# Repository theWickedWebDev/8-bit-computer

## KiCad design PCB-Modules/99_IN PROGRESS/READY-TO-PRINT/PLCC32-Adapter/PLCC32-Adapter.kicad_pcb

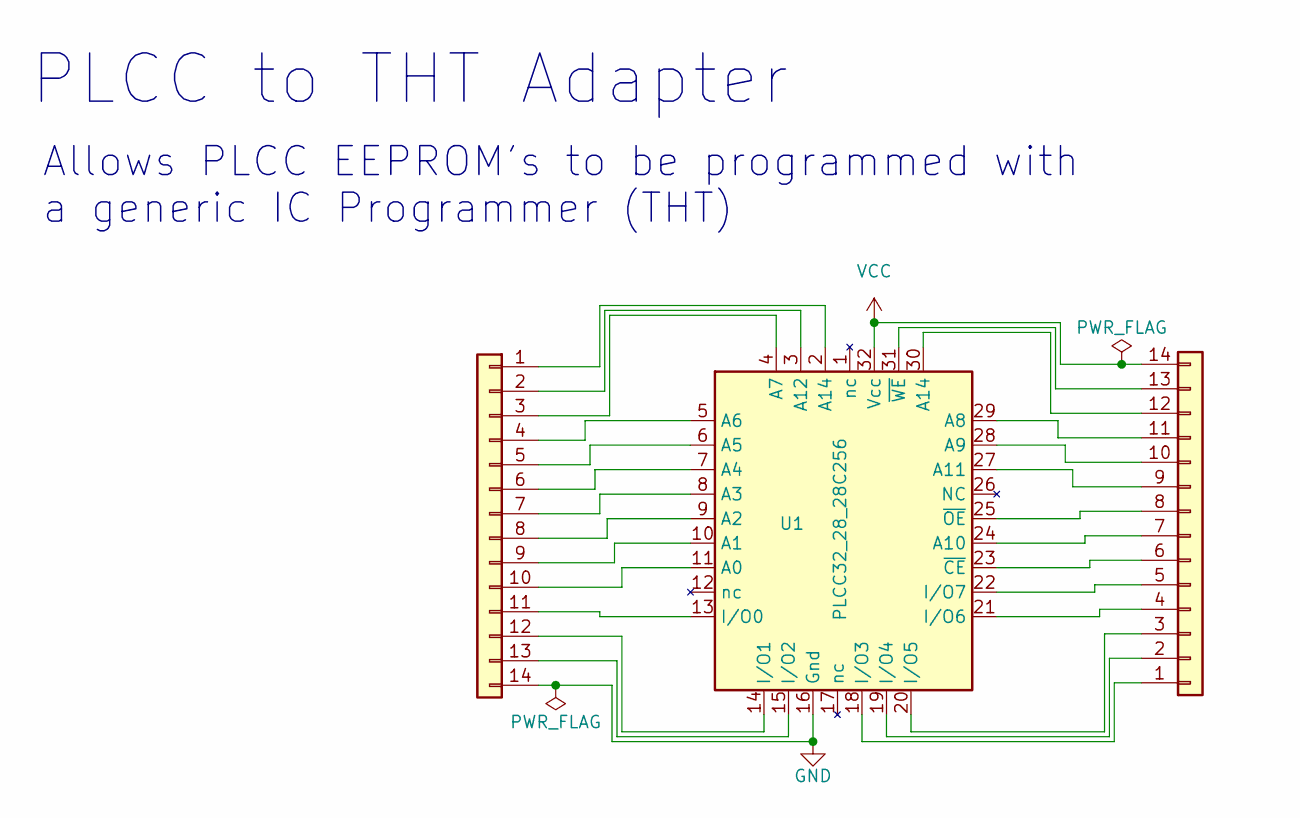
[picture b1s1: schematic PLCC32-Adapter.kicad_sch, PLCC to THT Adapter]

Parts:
J1, J2: Conn_01x14; PinHeader_1x14_P2.54mm_Vertical
U1: PLCC32_28_28C256; Microchip-32J-10_2001-B-IPC_A

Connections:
GND: J2.14, U1.16 (Gnd)
unnamed: J1.1, U1.18 (I/O3)
unnamed: J1.2, U1.19 (I/O4)
unnamed: J1.3, U1.20 (I/O5)
unnamed: J1.4, U1.21 (I/O6)
unnamed: J1.5, U1.22 (I/O7)
unnamed: J1.6, U1.23 (~CE)
unnamed: J1.7, U1.24 (A10)
unnamed: J1.8, U1.25 (~OE)
unnamed: J1.9, U1.27 (A11)
unnamed: J1.10, U1.28 (A9)
unnamed: J1.11, U1.29 (A8)
unnamed: J1.12, U1.30 (A14)
unnamed: J1.13, U1.31 (~WE)
unnamed: J2.1, U1.2 (A14)
unnamed: J2.2, U1.3 (A12)
unnamed: J2.3, U1.4 (A7)
unnamed: J2.4, U1.5 (A6)
unnamed: J2.5, U1.6 (A5)
unnamed: J2.6, U1.7 (A4)
unnamed: J2.7, U1.8 (A3)
unnamed: J2.8, U1.9 (A2)
unnamed: J2.9, U1.10 (A1)
unnamed: J2.10, U1.11 (A0)
unnamed: J2.11, U1.13 (I/O0)
unnamed: J2.12, U1.14 (I/O1)
unnamed: J2.13, U1.15 (I/O2)
VCC: J1.14, U1.32 (Vcc)

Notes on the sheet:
PLCC to THT Adapter
Allows PLCC EEPROM's to be programmed with a generic IC Programmer (THT)

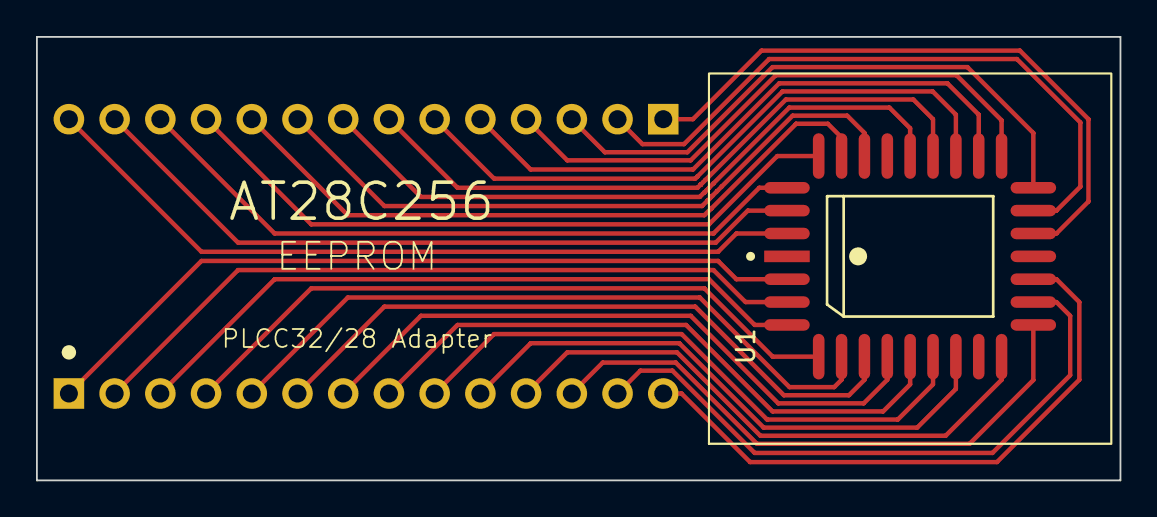
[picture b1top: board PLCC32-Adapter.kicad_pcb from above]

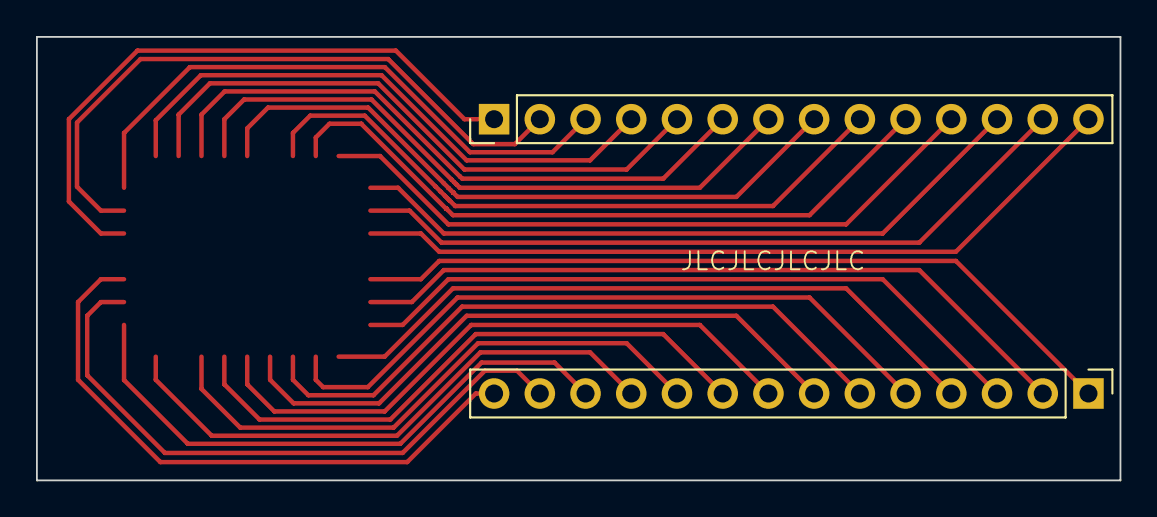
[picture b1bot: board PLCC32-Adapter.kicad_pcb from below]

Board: 2 copper layers, 60.2 x 24.6 mm, 3 parts (2 on the bottom side), 28 nets.

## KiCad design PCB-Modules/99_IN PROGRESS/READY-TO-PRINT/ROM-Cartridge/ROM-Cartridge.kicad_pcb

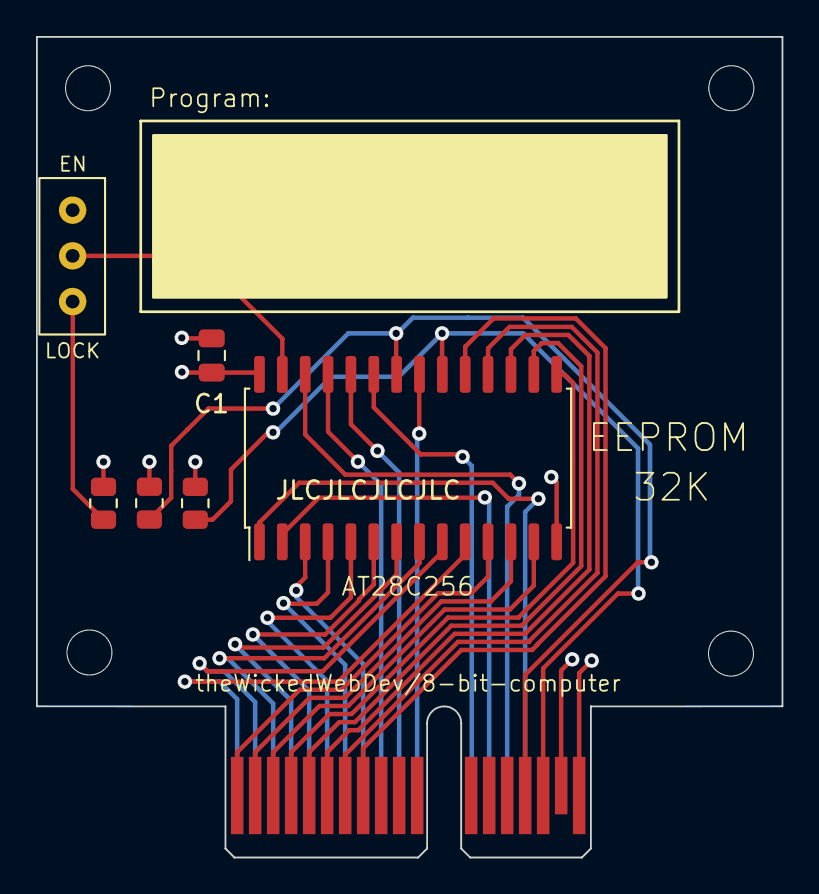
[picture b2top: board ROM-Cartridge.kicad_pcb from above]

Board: 4 copper layers, 41.4 x 45.6 mm, 7 parts (0 on the bottom side), 29 nets.

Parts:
C1: C; C_0805_2012Metric
J1: PCIE-Edge-Connect-036-02-X-D-RA_1; BUS_PCIexpress_x1
R1, R2, R3: R_Small_US; R_0805_2012Metric
SW1: SW_DPDT_x2; spdt-slide-switch
U1: 28C256; SOIC-28W_7.5x17.9mm_P1.27mm

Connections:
/A0: J1.A1 (A01), U1.10 (A0)
/A1: J1.A2 (A02), U1.9 (A1)
/A2: J1.A3 (A03), U1.8 (A2)
/A3: J1.A4 (A04), U1.7 (A3)
/A4: J1.A5 (A05), U1.6 (A4)
/A5: J1.A6 (A06), U1.5 (A5)
/A6: J1.A7 (A07), U1.4 (A6)
/A7: J1.A8 (A08), U1.3 (A7)
/A8: J1.A9 (A09), U1.25 (A8)
/A9: J1.A10, U1.24 (A9)
/A10: J1.A11, U1.21 (A10)
/A11: J1.A12, U1.23 (A11)
/A12: J1.A13, U1.2 (A12)
/A13: J1.A14, U1.26 (A13)
/A14: J1.A15, U1.1 (A14)
/D0: J1.B1 (B01), U1.11 (D0)
/D1: J1.B2 (B02), U1.12 (D1)
/D2: J1.B3 (B03), U1.13 (D2)
/D3: J1.B4 (B04), U1.15 (D3)
/D4: J1.B5 (B05), U1.16 (D4)
/D5: J1.B6 (B06), U1.17 (D5)
/D6: J1.B7 (B07), U1.18 (D6)
/D7: J1.B8 (B08), U1.19 (D7)
/~EN: J1.B16, R1.1, U1.20 (~CS)
/~READ: J1.B15, R2.1, U1.22 (~OE)
/~WRITE: R3.1, SW1.1 (A)
GND: C1.2, J1.B17, U1.14 (GND)
unnamed: SW1.2 (B), U1.27 (~WE)
VCC: C1.1, J1.B18, R1.2, R2.2, R3.2, U1.28 (VCC)

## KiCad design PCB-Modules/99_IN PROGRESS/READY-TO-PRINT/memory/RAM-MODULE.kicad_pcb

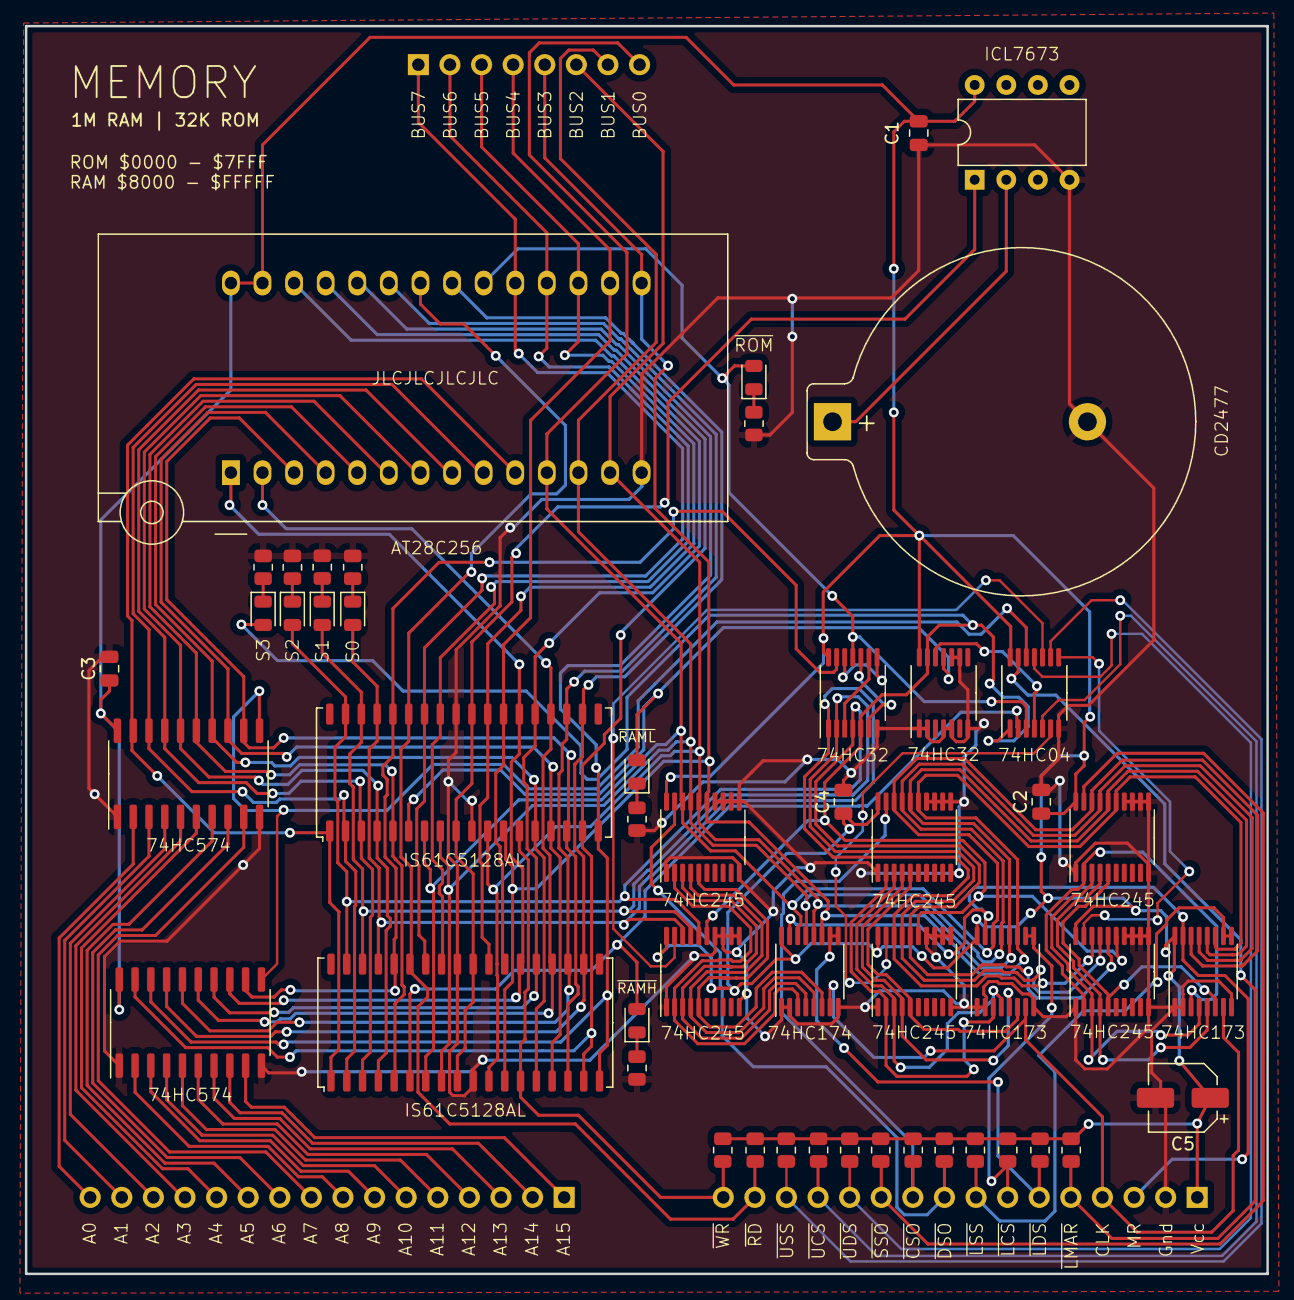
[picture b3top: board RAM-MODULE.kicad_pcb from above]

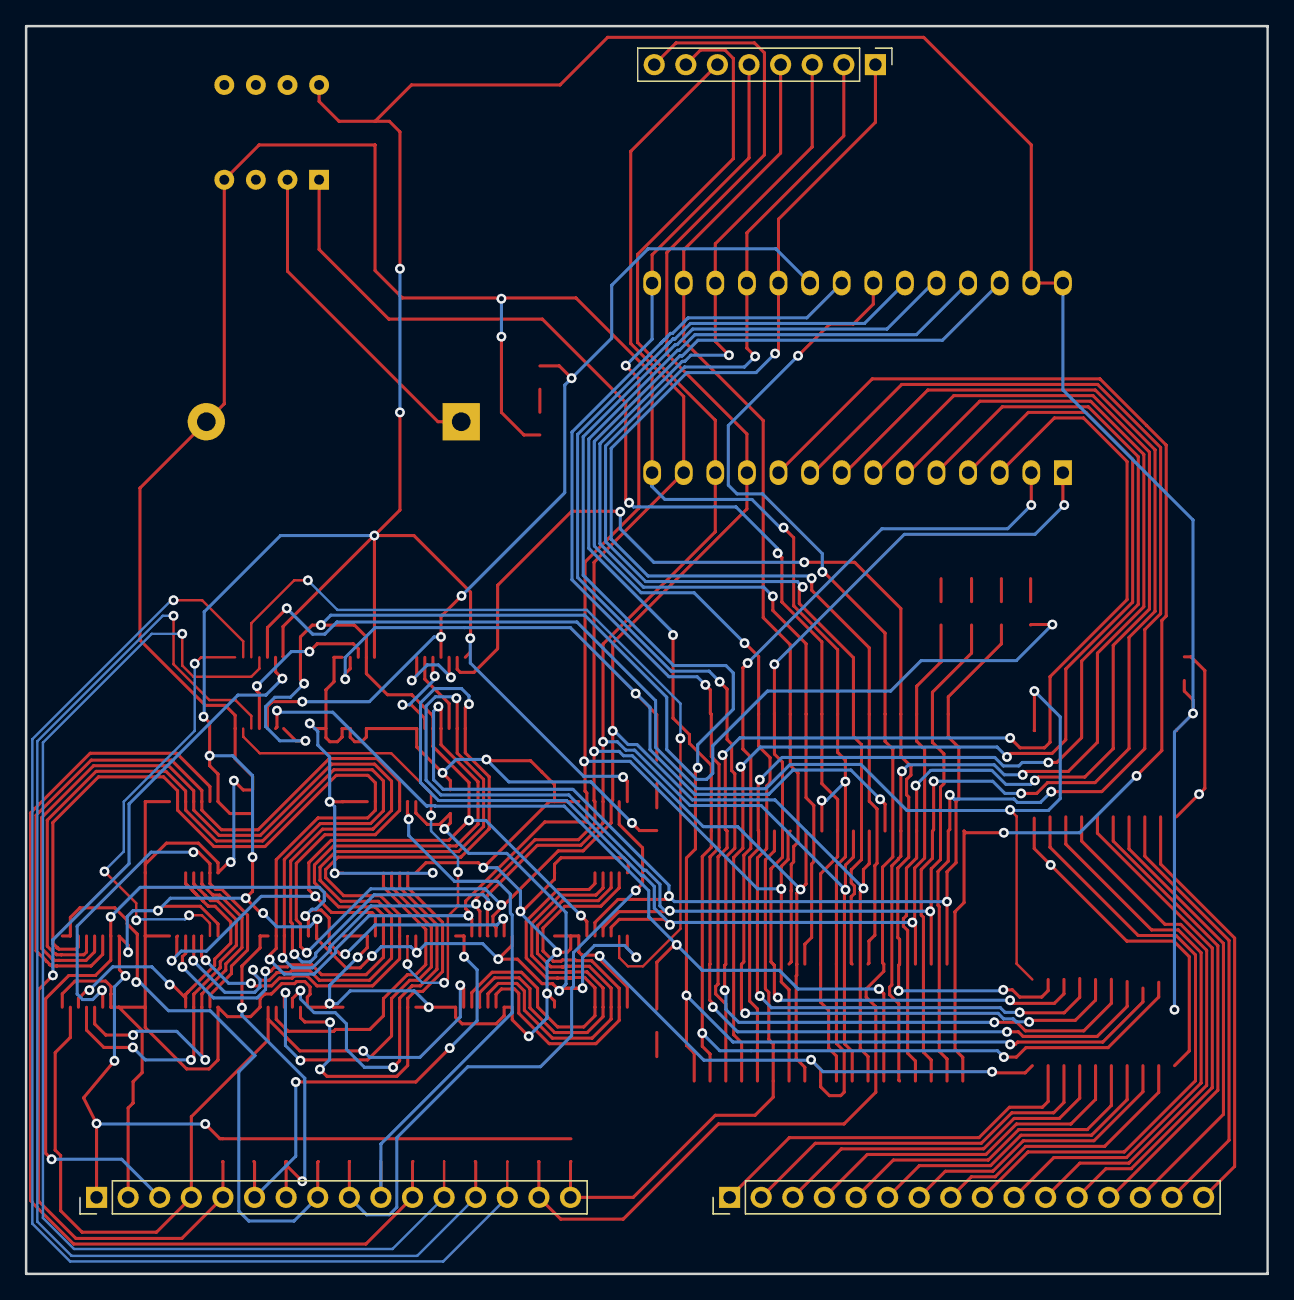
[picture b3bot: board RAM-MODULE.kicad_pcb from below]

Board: 4 copper layers, 99.8 x 100.3 mm, 53 parts (3 on the bottom side), 92 nets.

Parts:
BT1: Battery_Cell; BatteryHolder_Keystone_106_1x20mm
C1, C2, C3, C4: C; C_0805_2012Metric
C5: C_Polarized; CP_Elec_5x5.9
D3, D4, D5, D6, D7, D8, D9: LED; LED_0805_2012Metric
J1, J3: Conn_01x16; PinHeader_1x16_P2.54mm_Vertical
J2: Conn_01x08; PinHeader_1x08_P2.54mm_Vertical
R2, R3, R4, R5, R6, R7, R8, R9, R10, R11, R12, R13, R14, R15, R16, R17, R18, R19, R20: R_US; R_0805_2012Metric
U1: 28C256; DIP_Socket-28_W11.9_W12.7_W15.24_W17.78_W18.5_3M_228-1277-0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
U2, U4: 74LS574; SO-20_5.3x12.6mm_P1.27mm
U3, U5: IS61C5128AL-10KLI; SOJ-36_10.16x23.49mm_P1.27mm
U6, U9, U12: 74LS173; TSSOP-16_4.4x5mm_P0.65mm
U7, U8, U10, U11, U13, U14: 74LS245; TSSOP-20_4.4x6.5mm_P0.65mm
U15, U17: 74LS32; TSSOP-14_4.4x5mm_P0.65mm
U16: 74LS04; TSSOP-14_4.4x5mm_P0.65mm
U18: ICL7673; DIP-8_W7.62mm

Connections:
+5V: C1.1, C2.1, C3.1, C4.1, C5.1, J3.1, R2.1, R3.1, R4.1, R5.1, R6.1, R7.1, R8.1, R9.1, R10.1, R11.1, R12.1, R13.1, U1.27 (~WE), U1.28 (VCC), U2.20 (VCC), U4.20 (VCC), U6.16 (VCC), U7.20 (VCC), U8.20 (VCC), U9.16 (VCC), U10.20 (VCC), U11.20 (VCC), U12.16 (VCC), U13.20 (VCC), U14.20 (VCC), U15.14 (VCC), U16.14 (VCC), U17.14 (VCC), U18.8 (Vp)
ADDR_BUS0: J1.16, U2.2 (D0)
ADDR_BUS1: J1.15, U2.3 (D1)
ADDR_BUS2: J1.14, U2.4 (D2)
ADDR_BUS3: J1.13, U2.5 (D3)
ADDR_BUS4: J1.12, U2.6 (D4)
ADDR_BUS5: J1.11, U2.7 (D5)
ADDR_BUS6: J1.10, U2.8 (D6)
ADDR_BUS7: J1.9, U2.9 (D7)
ADDR_BUS8: J1.8, U4.2 (D0)
ADDR_BUS9: J1.7, U4.3 (D1)
ADDR_BUS10: J1.6, U4.4 (D2)
ADDR_BUS11: J1.5, U4.5 (D3)
ADDR_BUS12: J1.4, U4.6 (D4)
ADDR_BUS13: J1.3, U4.7 (D5)
ADDR_BUS14: J1.2, U4.8 (D6)
ADDR_BUS15: J1.1, U4.9 (D7)
BUS0: J2.8, U1.11 (D0), U3.7 (I/O0), U5.7 (I/O0), U6.14 (D0), U8.18 (B0), U9.14 (D0), U11.18 (B0), U12.14 (D0), U14.18 (B0)
BUS1: J2.7, U1.12 (D1), U3.8 (I/O1), U5.8 (I/O1), U6.13 (D1), U8.17 (B1), U9.13 (D1), U11.17 (B1), U12.13 (D1), U14.17 (B1)
BUS2: J2.6, U1.13 (D2), U3.11 (I/O2), U5.11 (I/O2), U6.12 (D2), U8.16 (B2), U9.12 (D2), U11.16 (B2), U12.12 (D2), U14.16 (B2)
BUS3: J2.5, U1.15 (D3), U3.12 (I/O3), U5.12 (I/O3), U6.11 (D3), U8.15 (B3), U9.11 (D3), U11.15 (B3), U12.11 (D3), U14.15 (B3)
BUS4: J2.4, U1.16 (D4), U3.25 (I/O4), U5.25 (I/O4)
BUS5: J2.3, U1.17 (D5), U3.26 (I/O5), U5.26 (I/O5)
BUS6: J2.2, U1.18 (D6), U3.29 (I/O6), U5.29 (I/O6)
BUS7: J2.1, U1.19 (D7), U3.30 (I/O7), U5.30 (I/O7)
CLOCK: J3.4, U6.7 (Cp), U9.7 (Cp), U12.7 (Cp)
GND: BT1.2 (-), C1.2, C2.2, C3.2, C4.2, C5.2, J3.2, R14.1, R15.1, R16.1, R17.1, R18.1, R19.1, R20.1, U1.14 (GND), U2.1 (OE), U2.10 (GND), U3.10 (GND), U3.28 (GND), U4.1 (OE), U4.10 (GND), U5.10 (GND), U5.28 (GND), U6.1 (Oe1), U6.2 (Oe2), U6.8 (GND), U7.1 (A->B), U7.10 (GND), U7.11 (B7), U7.12 (B6), U7.13 (B5), U7.14 (B4), U8.1 (A->B), U8.10 (GND), U8.11 (B7), U8.12 (B6), U8.13 (B5), U8.14 (B4), U9.1 (Oe1), U9.2 (Oe2), U9.8 (GND), U10.1 (A->B), U10.10 (GND), U10.11 (B7), U10.12 (B6), U10.13 (B5), U10.14 (B4), U11.1 (A->B), U11.10 (GND), U11.11 (B7), U11.12 (B6), U11.13 (B5), U11.14 (B4), U12.1 (Oe1), U12.2 (Oe2), U12.8 (GND), U13.1 (A->B), U13.10 (GND), U13.11 (B7), U13.12 (B6), U13.13 (B5), U13.14 (B4), U14.1 (A->B), U14.10 (GND), U14.11 (B7), U14.12 (B6), U14.13 (B5), U14.14 (B4), U15.7 (GND), U16.7 (GND), U17.1, U17.2, U17.4, U17.5, U17.7 (GND), U17.9, U17.10, U18.4 (Gnd)
MAR0: U1.10 (A0), U2.19 (Q0), U3.1 (A0), U5.1 (A0)
MAR1: U1.9 (A1), U2.18 (Q1), U3.2 (A1), U5.2 (A1)
MAR2: U1.8 (A2), U2.17 (Q2), U3.3 (A2), U5.3 (A2)
MAR3: U1.7 (A3), U2.16 (Q3), U3.4 (A3), U5.4 (A3)
MAR4: U1.6 (A4), U2.15 (Q4), U3.5 (A4), U5.5 (A4)
MAR5: U1.5 (A5), U2.14 (Q5), U3.14 (A5), U5.14 (A5)
MAR6: U1.4 (A6), U2.13 (Q6), U3.15 (A6), U5.15 (A6)
MAR7: U1.3 (A7), U2.12 (Q7), U3.16 (A7), U5.16 (A7)
MAR8: U1.25 (A8), U3.17 (A8), U4.19 (Q0), U5.17 (A8)
MAR9: U1.24 (A9), U3.18 (A9), U4.18 (Q1), U5.18 (A9)
MAR10: U1.21 (A10), U3.20 (A10), U4.17 (Q2), U5.20 (A10)
MAR11: U1.23 (A11), U3.21 (A11), U4.16 (Q3), U5.21 (A11)
MAR12: U1.2 (A12), U3.22 (A12), U4.15 (Q4), U5.22 (A12)
MAR13: U1.26 (A13), U3.23 (A13), U4.14 (Q5), U5.23 (A13)
MAR14: U1.1 (A14), U3.24 (A14), U4.13 (Q6), U5.24 (A14)
MAR15: U3.32 (A15), U4.12 (Q7), U5.32 (A15), U15.13
unnamed: BT1.1 (+), U18.2 (Vs)
unnamed: D3.1 (K), R14.2
unnamed: D4.1 (K), R15.2
unnamed: D5.1 (K), R16.2
unnamed: D6.1 (K), R17.2
unnamed: D7.1 (K), R18.2
unnamed: D8.1 (K), R19.2
unnamed: D9.1 (K), R20.2
unnamed: U6.3 (Q0), U7.2 (A0), U8.2 (A0)
unnamed: U6.4 (Q1), U7.3 (A1), U8.3 (A1)
unnamed: U6.5 (Q2), U7.4 (A2), U8.4 (A2)
unnamed: U6.6 (Q3), U7.5 (A3), U8.5 (A3)
unnamed: U9.3 (Q0), U10.2 (A0), U11.2 (A0)
unnamed: U9.4 (Q1), U10.3 (A1), U11.3 (A1)
unnamed: U9.5 (Q2), U10.4 (A2), U11.4 (A2)
unnamed: U9.6 (Q3), U10.5 (A3), U11.5 (A3)
unnamed: U12.3 (Q0), U13.2 (A0), U14.2 (A0)
unnamed: U12.4 (Q1), U13.3 (A1), U14.3 (A1)
unnamed: U12.5 (Q2), U13.4 (A2), U14.4 (A2)
unnamed: U12.6 (Q3), U13.5 (A3), U14.5 (A3)
unnamed: U15.3, U15.9
unnamed: U15.6, U15.10
unnamed: U15.8, U15.12
unnamed: U16.4, U17.12
unnamed: U2.11 (Cp), U4.11 (Cp), U16.12
RESET: J3.3, U6.15 (Mr), U9.15 (Mr), U12.15 (Mr)
SEG0: D3.2 (A), U3.33 (A16), U5.33 (A16), U7.18 (B0), U10.18 (B0), U13.18 (B0), U15.1
SEG1: D4.2 (A), U3.34 (A17), U5.34 (A17), U7.17 (B1), U10.17 (B1), U13.17 (B1), U15.2
SEG2: D5.2 (A), U3.35 (A18), U5.35 (A18), U7.16 (B2), U10.16 (B2), U13.16 (B2), U15.4
SEG3: D6.2 (A), U7.15 (B3), U10.15 (B3), U13.15 (B3), U15.5, U16.1, U17.13
USE_CODE_SEGMENT: U10.19 (CE), U16.6
USE_DATA_SEGMENT: U7.19 (CE), U16.10
USE_STACK_SEGMENT: U13.19 (CE), U16.8
VCC: U3.9 (VDD), U3.27 (VDD), U5.9 (VDD), U5.27 (VDD), U18.1 (VO)
~CODE_SEGMENT_OUT: J3.10, R8.2, U11.19 (CE)
~DATA_SEGMENT_OUT: J3.9, R9.2, U8.19 (CE)
~ENABLE_RAM_HIGH: D7.2 (A), U5.6 (~CE), U16.2
~ENABLE_RAM_LOW: D8.2 (A), U3.6 (~CE), U17.11
~ENABLE_ROM: D9.2 (A), U1.20 (~CS), U15.11, U16.3
~LATCH_CODE_SEGMENT: J3.7, R11.2, U9.9 (E1), U9.10 (E2)
~LATCH_DATA_SEGMENT: J3.6, R12.2, U6.9 (E1), U6.10 (E2)
~LATCH_MAR: J3.5, R13.2, U16.13
~LATCH_STACK_SEGMENT: J3.8, R10.2, U12.9 (E1), U12.10 (E2)
~READ: J3.15, R3.2, U1.22 (~OE), U3.31 (~OE), U5.31 (~OE)
~STACK_SEGMENT_OUT: J3.11, R7.2, U14.19 (CE)
~USE_CODE_SEGMENT: J3.13, R5.2, U16.5
~USE_DATA_SEGMENT: J3.12, R6.2, U16.11
~USE_STACK_SEGMENT: J3.14, R4.2, U16.9
~WRITE: J3.16, R2.2, U3.13 (~WE), U5.13 (~WE)

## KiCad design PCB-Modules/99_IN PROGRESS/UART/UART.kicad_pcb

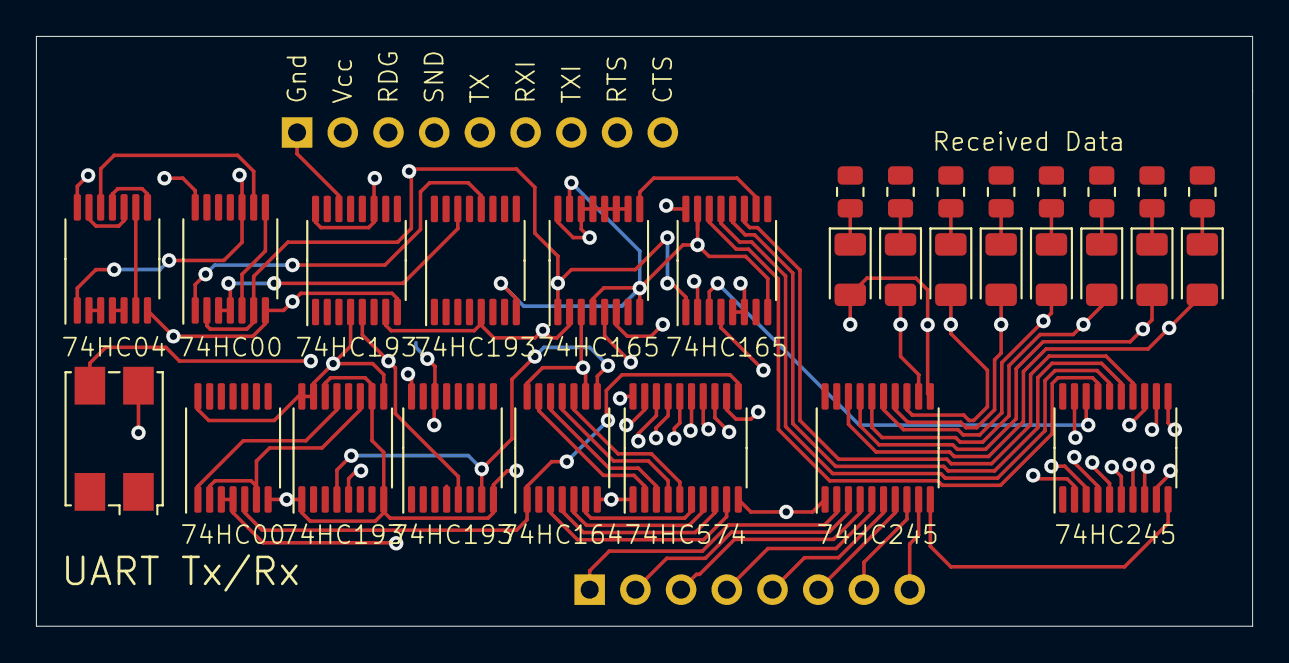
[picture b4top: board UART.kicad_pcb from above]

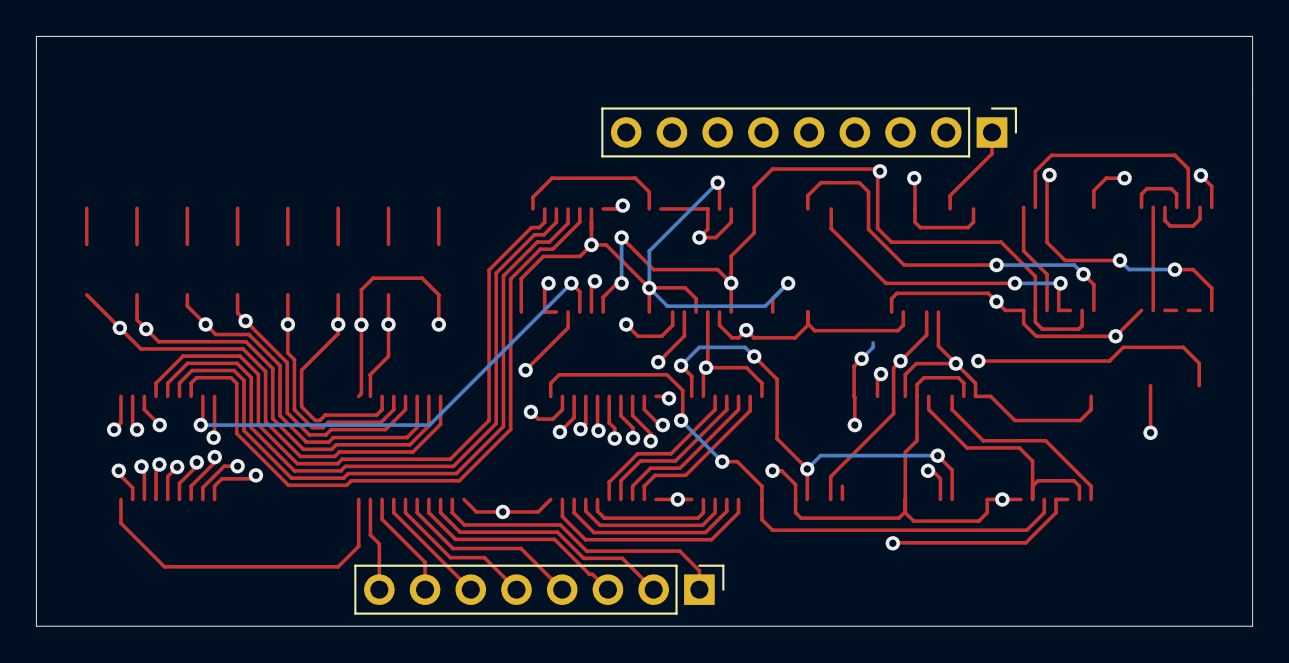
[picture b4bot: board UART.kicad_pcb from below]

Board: 4 copper layers, 67.6 x 32.8 mm, 32 parts (2 on the bottom side), 64 nets.

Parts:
D1, D2, D3, D4, D5, D6, D7, D8: LED; LED_1206_3216Metric
J1: Conn_01x09; PinHeader_1x09_P2.54mm_Vertical
J2: Conn_01x08; PinHeader_1x08_P2.54mm_Vertical
R1, R2, R3, R4, R5, R6, R7, R8: 1kohm; R_0805_2012Metric
U1: full-can-crystal; Crystal_SMD_7050-4Pin_7.0x5.0mm
U2, U3, U10, U11: 74LS193; TSSOP-16_4.4x5mm_P0.65mm
U4, U5: 74LS165; TSSOP-16_4.4x5mm_P0.65mm
U6, U14: 74HC245PW,118; TSSOP-20_4.4x6.5mm_P0.65mm
U7: 74LS04; TSSOP-14_4.4x5mm_P0.65mm
U8, U9: 74LS00; TSSOP-14_4.4x5mm_P0.65mm
U12: 74LS164; TSSOP-14_4.4x5mm_P0.65mm
U13: 74LS574; TSSOP-20_4.4x6.5mm_P0.65mm

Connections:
BUS0: J2.1, U6.2, U14.2
BUS1: J2.2, U6.3, U14.3
BUS2: J2.3, U6.4, U14.4
BUS3: J2.4, U6.5, U14.5
BUS4: J2.5, U6.6, U14.6
BUS5: J2.6, U6.7, U14.7
BUS6: J2.7, U6.8, U14.8
BUS7: J2.8, U6.9, U14.9
CLK: U2.7, U3.5, U4.2, U5.2
CLR: U3.14, U8.3, U8.4
CO: U3.12, U8.1
GND: J1.1, R1.2, R2.2, R3.2, R4.2, R5.2, R6.2, R7.2, R8.2, U1.2, U2.8, U2.14, U3.8, U4.8, U4.15, U5.4, U5.8, U5.15, U6.10, U7.7, U8.7, U9.7, U10.1, U10.8, U10.10, U10.14, U11.8, U12.7, U13.1, U13.10, U14.1, U14.10
unnamed: D1.1, R1.1
unnamed: D2.1, R2.1
unnamed: D3.1, R3.1
unnamed: D4.1, R4.1
unnamed: D5.1, R5.1
unnamed: D6.1, R6.1
unnamed: D7.1, R7.1
unnamed: D8.1, R8.1
unnamed: U1.3, U2.5, U11.5
unnamed: U4.10, U5.9
unnamed: U7.2, U7.3
unnamed: U7.4, U7.5
unnamed: U7.6, U7.9
unnamed: U7.10, U7.13
unnamed: U7.8, U7.11
unnamed: U7.12, U8.9
unnamed: U8.5, U8.8
unnamed: U10.4, U11.7, U12.8
unnamed: U9.2, U9.6, U10.11
unnamed: U9.1, U10.13
RECEIVING_DATA: J1.9, U9.3, U9.4, U11.14
RX0: U4.3, U6.18
RX1: U4.14, U6.17
RX2: U4.13, U6.16
RX3: U4.12, U6.15
RX4: U4.11, U6.14
RX5: U5.6, U6.13
RX6: U5.5, U6.12
RX7: U4.4, U6.11
RX_IN_CABLE: J1.5, U4.9
SEND_DATA: J1.3, U7.1, U8.10
SH~LD: J1.8, U4.1, U5.1, U8.2, U8.6
TX0: U12.13, U13.2
TX1: U12.12, U13.3
TX2: U12.11, U13.4
TX3: U12.10, U13.5
TX4: U12.6, U13.6
TX5: U12.5, U13.7
TX6: U12.4, U13.8
TX7: U12.3, U13.9
TXQ0: D8.2, U13.19, U14.18
TXQ1: D7.2, U13.18, U14.17
TXQ2: D6.2, U13.17, U14.16
TXQ3: D5.2, U13.16, U14.15
TXQ4: D4.2, U13.15, U14.14
TXQ5: D3.2, U13.14, U14.13
TXQ6: D2.2, U13.13, U14.12
TXQ7: D1.2, U13.12, U14.11
TX_IN_CABLE: J1.6, U9.5, U12.1, U13.11
VCC: J1.2, U1.4, U2.4, U2.11, U2.16, U3.4, U3.11, U3.16, U4.5, U4.6, U4.16, U5.3, U5.10, U5.11, U5.12, U5.13, U5.14, U5.16, U6.1, U6.20, U7.14, U8.14, U9.14, U10.5, U10.9, U10.15, U10.16, U11.4, U11.11, U11.16, U12.2, U12.9, U12.14, U13.20, U14.20
~SEND_RECEIVED_DATA_TO_BUS: J1.7, U14.19
~TRANSMIT_DATA_FROM_BUS: J1.4, U6.19

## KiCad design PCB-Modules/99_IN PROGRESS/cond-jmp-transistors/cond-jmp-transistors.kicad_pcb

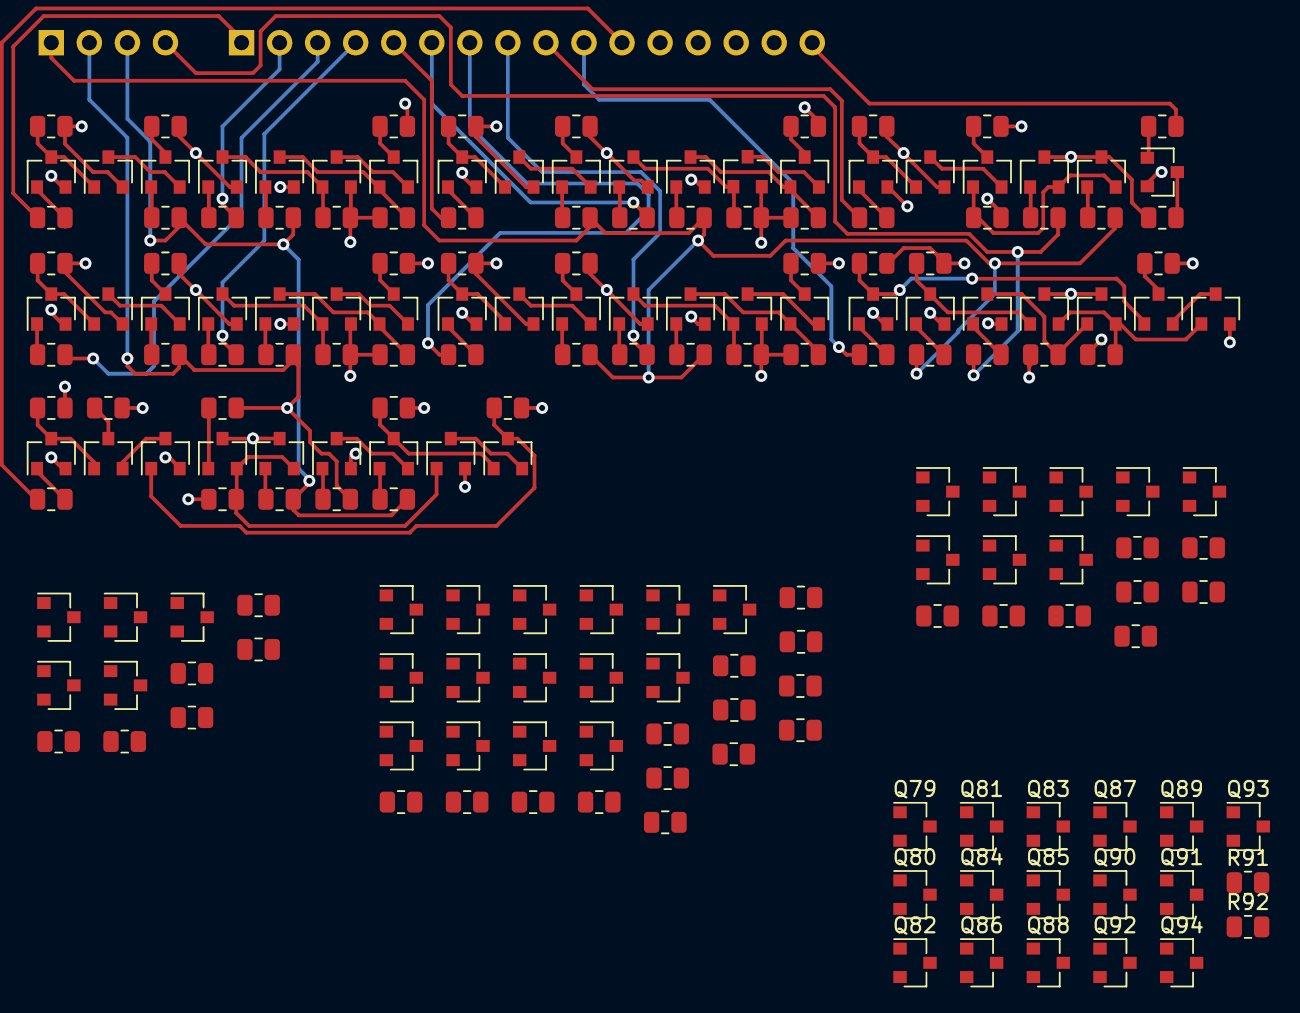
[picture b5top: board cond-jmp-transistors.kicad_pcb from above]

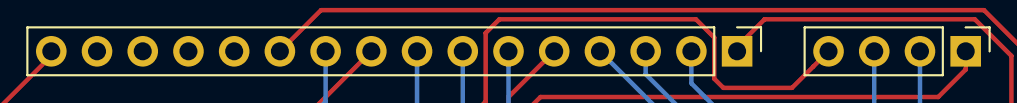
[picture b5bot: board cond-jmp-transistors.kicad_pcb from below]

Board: 4 copper layers, 188 parts (2 on the bottom side), 135 nets.

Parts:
J1: Conn_01x04; PinHeader_1x04_P2.54mm_Vertical
J2: Conn_01x16; PinHeader_1x16_P2.54mm_Vertical
Q1, Q2, Q3, Q4, Q5, Q6, Q7, Q8, Q9, Q10, Q11, Q12, Q13, Q14, Q15, Q16, Q17, Q18, Q19, Q20, Q21, Q22, Q23, Q24, Q25, Q26, Q27, Q28, Q29, Q30, Q31, Q32, Q33, Q34, Q35, Q36, Q37, Q38, Q39, Q40, Q41, Q42, Q43, Q44, Q45, Q46, Q47, Q48, Q49, Q50, Q51, Q52, Q53, Q54, Q55, Q56, Q57, Q58, Q59, Q60, Q61, Q62, Q63, Q64, Q65, Q66, Q67, Q68, Q69, Q70, Q71, Q72, Q73, Q74, Q75, Q76, Q77, Q78, Q79, Q80, Q81, Q82, Q83, Q84, Q85, Q86, Q87, Q88, Q89, Q90, Q91, Q92, Q93, Q94: PMBT2222; SOT-23
R1, R2, R5, R7, R10, R11, R14, R16, R19, R20, R23, R25, R28, R29, R32, R34, R37, R41, R42, R43, R45, R46, R47, R54, R55, R57, R59, R60, R63, R66, R68, R69, R70, R73, R74, R79, R83, R84, R87: 10kohm; R_0805_2012Metric
R3, R4, R6, R8, R9, R12, R13, R15, R17, R18, R21, R22, R24, R26, R27, R30, R31, R33, R35, R36, R38, R39, R40, R44, R48, R49, R50, R51, R52, R53, R56, R58, R61, R62, R64, R65, R67, R71, R72, R75, R76, R77, R78, R80, R81, R82, R85, R86, R88, R89, R90, R91, R92: 3.9kohm; R_0805_2012Metric

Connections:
CARRY_FLAG: J1.4, R41.1, R47.1
GND: Q1.2, Q2.2, Q3.2, Q8.2, Q9.2, Q10.2, Q15.2, Q16.2, Q17.2, Q22.2, Q23.2, Q24.2, Q29.2, Q34.2, Q35.2, Q36.2, Q37.2, Q42.2, Q47.2, Q51.2, Q56.2, Q57.2, Q66.2, Q68.2, Q71.2, Q72.2, Q79.2, R8.2, R9.2, R17.2, R18.2, R26.2, R27.2, R35.2, R36.2, R39.1, R40.2, R51.1, R52.2, R53.1, R58.2, R62.2, R65.1, R67.2, R75.2, R76.2, R77.1, R78.2, R82.2, R88.2, R89.2, R90.2, R92.1
J: Q34.3, Q90.1, R44.1
JA_JNBE: Q40.3, Q92.1, R52.1
JBE_JNA: Q31.3, Q91.1, R40.1
JB_JNAE_JC: Q26.3, Q83.1, R35.1
JE_JZ: Q19.3, Q85.1, R26.1
JGE_JNL: Q70.3, Q81.1, R82.1
JG_JNLE: Q78.3, Q80.1, R90.1
JLE_JNG: Q54.3, Q93.1, R67.1
JL_JNGE: Q50.3, Q94.1, R62.1
JNB_JAE_JNC: Q28.3, Q82.1, R36.1
JNE_JNZ: Q21.3, Q84.1, R27.1
JNO: Q7.3, Q89.1, R9.1
JNS: Q14.3, Q87.1, R18.1
JO: Q5.3, Q88.1, R8.1
JS: Q12.3, Q86.1, R17.1
LOAD_PROGRAM_COUNTER: Q79.3, R91.1
unnamed: Q1.1, R1.2
unnamed: Q1.3, Q6.1, R3.1
unnamed: Q2.1, R2.2
unnamed: Q2.3, Q4.1, R4.1
unnamed: Q3.1, R5.2
unnamed: Q3.3, Q7.1, R6.1
unnamed: Q4.3, Q5.2
unnamed: Q5.1, R7.2
unnamed: Q6.3, Q7.2
unnamed: Q8.1, R10.2
unnamed: Q9.1, R11.2
unnamed: Q10.1, R14.2
unnamed: Q10.3, Q14.1, R15.1
unnamed: Q9.3, Q11.1, R13.1
unnamed: Q11.3, Q12.2
unnamed: Q12.1, R16.2
unnamed: Q8.3, Q13.1, R12.1
unnamed: Q13.3, Q14.2
unnamed: Q15.1, R19.2
unnamed: Q15.3, Q20.1, R21.1
unnamed: Q16.1, R20.2
unnamed: Q16.3, Q18.1, R22.1
unnamed: Q17.1, R23.2
unnamed: Q17.3, Q21.1, R24.1
unnamed: Q18.3, Q19.2
unnamed: Q19.1, R25.2
unnamed: Q20.3, Q21.2
unnamed: Q22.1, R28.2
unnamed: Q22.3, Q27.1, R30.1
unnamed: Q23.1, R29.2
unnamed: Q23.3, Q25.1, R31.1
unnamed: Q24.1, R32.2
unnamed: Q24.3, Q28.1, R33.1
unnamed: Q25.3, Q26.2
unnamed: Q26.1, R34.2
unnamed: Q27.3, Q28.2
unnamed: Q29.1, R37.2
unnamed: Q29.3, Q30.1, R38.1
unnamed: Q30.3, Q31.2
unnamed: Q31.1, Q32.2, Q33.2, R39.2
unnamed: Q32.1, R41.2
unnamed: Q33.1, R42.2
unnamed: Q34.1, R43.2
unnamed: Q35.1, R45.2
unnamed: Q35.3, Q40.1, R48.1
unnamed: Q36.1, R46.2
unnamed: Q36.3, Q38.1, R49.1
unnamed: Q37.1, R47.2
unnamed: Q37.3, Q39.1, R50.1
unnamed: Q38.2, Q39.2, Q41.1, R51.2
unnamed: Q40.2, Q41.3
unnamed: Q42.1, R54.2
unnamed: Q42.3, Q50.1, R56.1
unnamed: Q43.1, R55.2
unnamed: Q43.2, Q44.2, Q45.1, R53.2
unnamed: Q44.1, R57.2
unnamed: Q45.3, Q46.2
unnamed: Q46.1, Q48.3, R61.2
unnamed: Q47.1, R59.2
unnamed: Q47.3, Q48.2
unnamed: Q48.1, R60.2
unnamed: Q49.3, Q50.2
unnamed: Q51.1, R63.2
unnamed: Q51.3, Q52.1, R64.1
unnamed: Q52.3, Q54.2
unnamed: Q53.1, R66.2
unnamed: Q53.2, Q54.1, Q55.2, R65.2
unnamed: Q55.1, R68.2
unnamed: Q56.1, R69.2
unnamed: Q56.3, Q61.1, R71.1
unnamed: Q57.1, R70.2
unnamed: Q57.3, Q59.1, R72.1
unnamed: Q58.1, R73.2
unnamed: Q58.3, Q60.2
unnamed: Q59.3, Q61.2
unnamed: Q60.1, R74.2
unnamed: Q60.3, Q62.1, Q66.1, R75.1
unnamed: Q61.3, Q63.1, Q67.1, R76.1
unnamed: Q62.2, Q63.2, Q64.1, R77.2
unnamed: Q64.3, Q65.2
unnamed: Q66.3, Q67.2
unnamed: Q67.3, R80.2
unnamed: Q68.1, R79.2
unnamed: Q68.3, Q70.1, R81.1
unnamed: Q69.3, Q70.2
unnamed: Q71.1, R83.2
unnamed: Q71.3, Q78.1, R85.1
unnamed: Q72.1, R84.2
unnamed: Q72.3, Q76.1, R86.1
unnamed: Q73.3, Q74.2
unnamed: Q74.1, R87.2
unnamed: Q74.3, Q75.1, R88.1
unnamed: Q75.3, Q76.2
unnamed: Q76.3, Q77.1, R89.1
unnamed: Q77.3, Q78.2
unnamed: Q79.1, Q80.2, Q81.2, Q82.2, Q83.2, Q84.2, Q85.2, Q86.2, Q87.2, Q88.2, Q89.2, Q90.2, Q91.2, Q92.2, Q93.2, Q94.2, R92.2
OVERFLOW_FLAG: J1.3, R5.1, R7.1, R57.1, R60.1, R69.1, R73.1
SF<>OF: Q46.3, Q49.1, R58.1, R68.1
SF=OF: Q65.3, Q69.1, Q73.1, R78.1
SIGN_FLAG: J1.2, R14.1, R16.1, R55.1, R59.1, R70.1, R74.1
VCC: Q4.2, Q6.2, Q11.2, Q13.2, Q18.2, Q20.2, Q25.2, Q27.2, Q30.2, Q32.3, Q33.3, Q38.3, Q39.3, Q41.2, Q43.3, Q44.3, Q45.2, Q49.2, Q52.2, Q53.3, Q55.3, Q58.2, Q59.2, Q62.3, Q63.3, Q64.2, Q69.2, Q73.2, Q75.2, Q77.2, Q80.3, Q81.3, Q82.3, Q83.3, Q84.3, Q85.3, Q86.3, Q87.3, Q88.3, Q89.3, Q90.3, Q91.3, Q92.3, Q93.3, Q94.3, R3.2, R4.2, R6.2, R12.2, R13.2, R15.2, R21.2, R22.2, R24.2, R30.2, R31.2, R33.2, R38.2, R44.2, R48.2, R49.2, R50.2, R56.2, R61.1, R64.2, R71.2, R72.2, R80.1, R81.2, R85.2, R86.2, R91.2
ZERO_FLAG: J1.1, R23.1, R25.1, R32.1, R34.1, R42.1, R46.1, R66.1, R84.1, R87.1
~J: J2.16, R43.1
~JA_JNBE: J2.10, R45.1
~JBE_JNA: J2.9, R37.1
~JB_JNAE_JC: J2.7, R29.1
~JE_JZ: J2.5, R20.1
~JGE_JNL: J2.13, R79.1
~JG_JNLE: J2.14, R83.1
~JLE_JNG: J2.12, R63.1
~JL_JNGE: J2.11, R54.1
~JNB_JAE_JNC: J2.8, R28.1
~JNE_JNZ: J2.6, R19.1
~JNO: J2.2, R1.1
~JNS: J2.4, R10.1
~JO: J2.1, R2.1
~JS: J2.3, R11.1
